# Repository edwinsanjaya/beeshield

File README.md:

# Beeshield

## Sensors

This 'shield' connects the following sensors to the Smart Citizen base kit - [input pin wiki page](https://github.com/fablabbcn/Smart-Citizen-Kit/wiki/Making-a-Shield)

* 1 x DHT22 Temperature and Humidity Sensor
* 3+ x DS18B20 Digital Temperature Sensors

The three inputs for the DS18B20 aren't actually necessary, although the board works perfectly fine using them as-is, you can daisy-chain loads of these sensors together meaning that they only require a single input pin. They are a relic from using previous sensors and time constraints meant that they stayed as 3 pins.

The DHT22 is a strange beast. There are different versions of it. Some will happily run at 3.3V, the ones that I encountered will only run at 5V, however, there is a 'hack'. If you flagrantly ignore the following datasheet diagram

 and connect pin 3 to ground, along with pin 4, it seems to work. Keep in mind that this is a very slow sensor, I wouldn't recommend taking readings from it any faster than once every few seconds.
 
## Connections

You may notice that 2 of the last pins on the 12 pin connection aren't actually connected to anything, it's just that there are 6 pins on each header. By all means use 10 pins instead.

## Milling

I haven't tested the circuit PNGs above and my memory is a bit rusty. Please check that the borders are ok and that they are a reasonable size (in mm) in Fab Modules before milling.

## Misc

Feel free to ignore the `misc` folder, I was just dumping related stuff in there.

### Other Information

You may? find some insights here although I was quite delirious from lack of sleep when the page was written!
[http://academy.cba.mit.edu/2013/students/rees.john/input-devices/](http://academy.cba.mit.edu/2013/students/rees.john/input-devices/)

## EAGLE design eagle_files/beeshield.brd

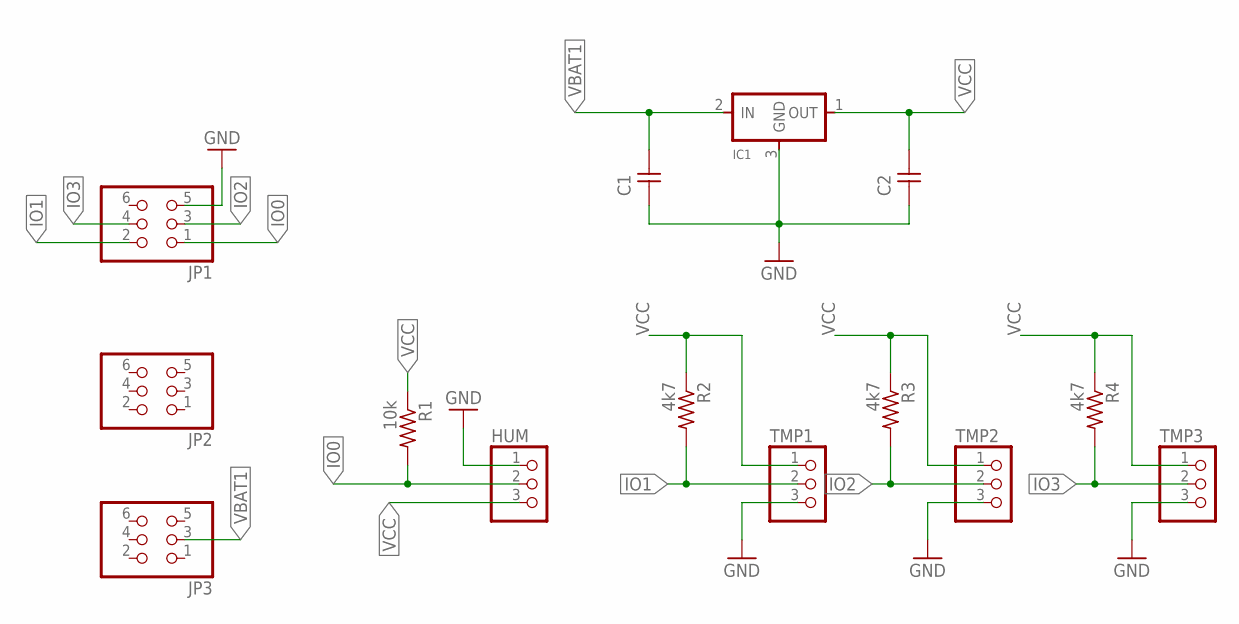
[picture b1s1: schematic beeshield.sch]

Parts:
C1, C2: UNPOLARIZED_CAPACITOR1206; 1206
HUM: PINHD-1X3; 1X03
IC1: REGULATORSOT23; SOT23
JP1, JP2, JP3: PINHD-2X3-SMD; 2X03SMD
R1: 10k; 1206
R2, R3, R4: 4k7; 1206
TMP1, TMP2, TMP3: PINHD-1X3; 1X03

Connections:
GND: C1.1, C2.1, HUM.1, IC1.3 (GND), JP1.5, TMP1.3, TMP2.3, TMP3.3
IO0: HUM.2, JP1.1, R1.2
IO1: JP1.2, R2.2, TMP1.2
IO2: JP1.3, R3.2, TMP2.2
IO3: JP1.4, R4.2, TMP3.2
VBAT1: C1.2, IC1.2 (IN), JP3.3
VCC: C2.2, HUM.3, IC1.1 (OUT), R1.1, R2.1, R3.1, R4.1, TMP1.1, TMP2.1, TMP3.1

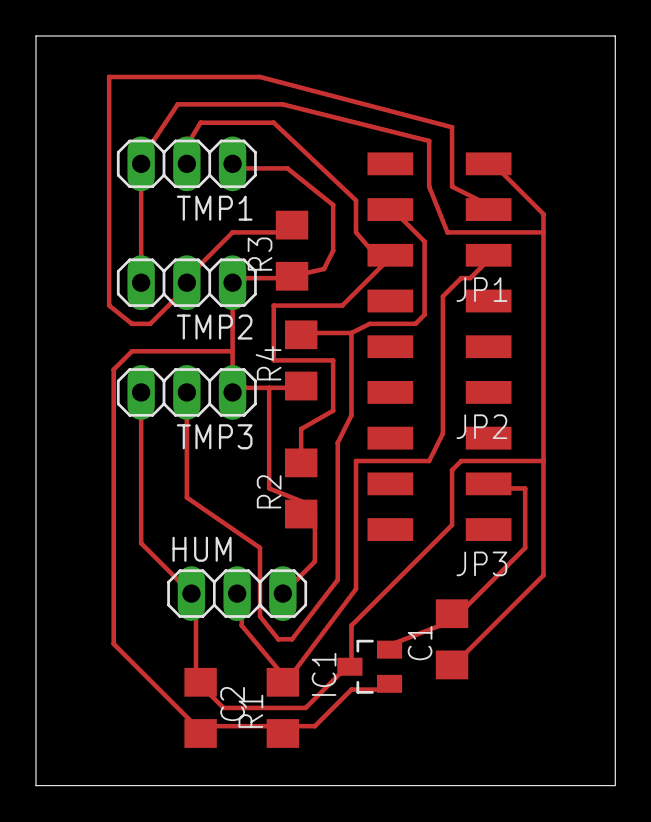
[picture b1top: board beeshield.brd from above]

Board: 2 copper layers, 32.2 x 41.6 mm, 14 parts (0 on the bottom side), 7 nets.

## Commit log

2013-09-27 new images
2013-09-27 new milling image
2013-09-27 new eagle files
